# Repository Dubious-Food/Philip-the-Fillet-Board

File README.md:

# Philip the Fillet Board
## Description 
This is a 4-key macropad I made for general shortcuts and volume control. It features 4 addressable leds, 6 clippies, a 3d-printed case, and rotary encoder.

## PCB
Here is the pcb and schematic that I made in Kicad.
Schematic            |  PCB
:-------------------------:|:-------------------------:
    |   

## Case
The macropad is mounted sandwich-style and is connected with M3x16mm screws. The case also features multiple clippies.
Case            |       
:-------------------------:|

## BOM
- 1x SEEEDUINO XIAO RP2040
- 4x  SK6812 MINI-E LEDs
- 4x MX-Style switches
- 1x EC11 Rotary encoders
- 5x through-hole 1N4148 Diodes
- 4x white blank DSA keycaps
- 4x M3x16mm screws
- 1x PCB
- 1x top case
- 1x bottom case

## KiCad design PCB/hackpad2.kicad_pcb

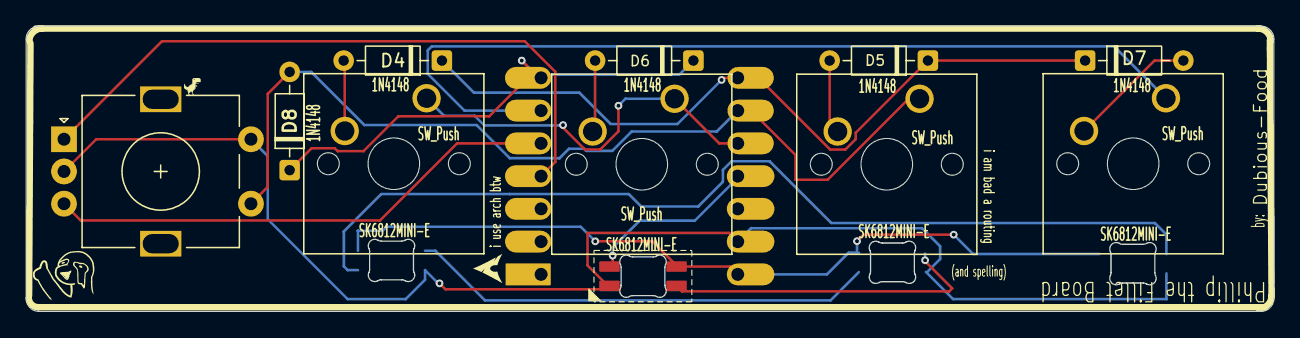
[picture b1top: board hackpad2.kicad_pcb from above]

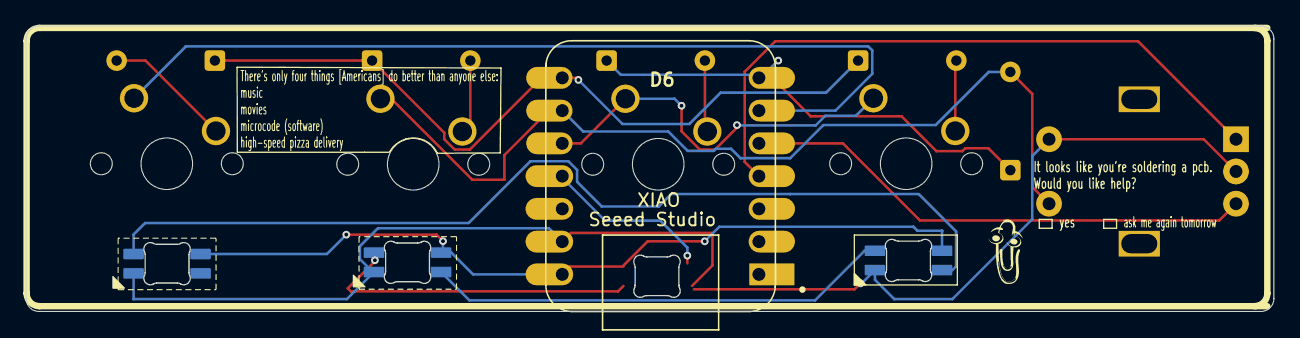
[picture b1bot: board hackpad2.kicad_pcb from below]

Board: 2 copper layers, 96.7 x 22.1 mm, 15 parts (2 on the bottom side), 17 nets.

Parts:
D2, D6#2, D8#2, D10: SK6812MINI-E; SK6812MINI-E_fixed
D4, D4#2, D6, D7, D8: 1N4148; D_DO-35_SOD27_P7.62mm_Horizontal
SW1, SW2, SW3, SW4: SW_Push; SW_Cherry_MX_1.00u_PCB
SW5: RotaryEncoder_Switch; RotaryEncoder_Alps_EC11E-Switch_Vertical_H20mm
U1: MOUDLE-SEEEDUINO-XIAO; XIAO-Generic-Hybrid-14P-2.54-21X17.8MM

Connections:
COL0: SW1.1, SW2.1, U1.10 (PA5_A9_D9_MISO)
COL1: D8.2 (A), SW4.1, SW5.S1, U1.9 (PA7_A8_D8_SCK)
COL2: SW3.1, U1.6 (PA9_A5_D5_SCL)
GND: D2.3 (VSS), D6#2.3 (VSS), D8#2.3 (VSS), D10.3 (VSS), SW5.C, SW5.S2, U1.13 (GND)
LED: D6#2.4 (DIN), U1.11 (PA6_A10_D10_MOSI)
unnamed: D2.2 (DOUT), D8#2.4 (DIN)
unnamed: D8#2.2 (DOUT), D10.4 (DIN)
unnamed: D2.4 (DIN), D6#2.2 (DOUT)
unnamed: D4#2.2 (A), SW1.2
unnamed: D4.2 (A), SW4.2
unnamed: D6.2 (A), SW2.2
unnamed: D7.2 (A), SW3.2
ROT1A: SW5.A, U1.4 (PA11_A3_D3)
ROT1B: SW5.B, U1.5 (PA8_A4_D4_SDA)
ROW0: D4.1 (K), D4#2.1 (K), D7.1 (K), U1.8 (PB09_A7_D7_RX)
ROW1: D6.1 (K), D8.1 (K), U1.7 (PB08_A6_D6_TX)
VCC: D2.1 (VDD), D6#2.1 (VDD), D8#2.1 (VDD), D10.1 (VDD), U1.14 (5V)

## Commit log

2026-03-24 Rename Screenshot_20260323_210312.png to Photos/Screenshot_20260323_210312.png
2026-03-24 Rename Screenshot_20260323_210336.png to Photos/Screenshot_20260323_210336.png
2026-03-24 Rename Screenshot_20260323_234545.png to Photos/Screenshot_20260323_234545.png
2026-03-24 Rename Screenshot_20260323_213049.png to Photos/Screenshot_20260323_213049.png
2026-03-24 Rename Screenshot_20260323_213028.png to Photos/Screenshot_20260323_213028.png
2026-03-24 Rename Screenshot_20260323_210346.png to Photos/Screenshot_20260323_210346.png
2026-03-24 Rename Part Studio 1.step to CAD/Part Studio 1.step
2026-03-24 Rename Okayish-Macropad.step to CAD/Okayish-Macropad.step
2026-03-24 Rename hackpad2.kicad_pcb to PCB/hackpad2.kicad_pcb
2026-03-24 Rename hackpad2.kicad_pro to PCB/hackpad2.kicad_pro
2026-03-24 Rename hackpad2.kicad_sch to PCB/hackpad2.kicad_sch
2026-03-24 Rename gerbers.zip to Production/gerbers.zip
2026-03-31 Create txt
